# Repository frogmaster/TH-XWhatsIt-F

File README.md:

Derived from:

https://github.com/listofoptions/TH-XWhatsIt

through hole implementation of the capsense controllers by XWhatsIt
(Tom Wong-Cornell). original liscencure holds, as well as CERN OSH
(compatible license).

original implementation of Tom Wong-Cornell's controller documented here

http://downloads.cornall.co/ibm-capsense-usb-web/ibm-capsense-usb.html

component documentation is supplied, working theory of operation is under
the previous link.

Layout changed to accomodate IBM Model F PC/AT keyboard, mainly because i have that one. 
May fit other model F-s with similar setup.

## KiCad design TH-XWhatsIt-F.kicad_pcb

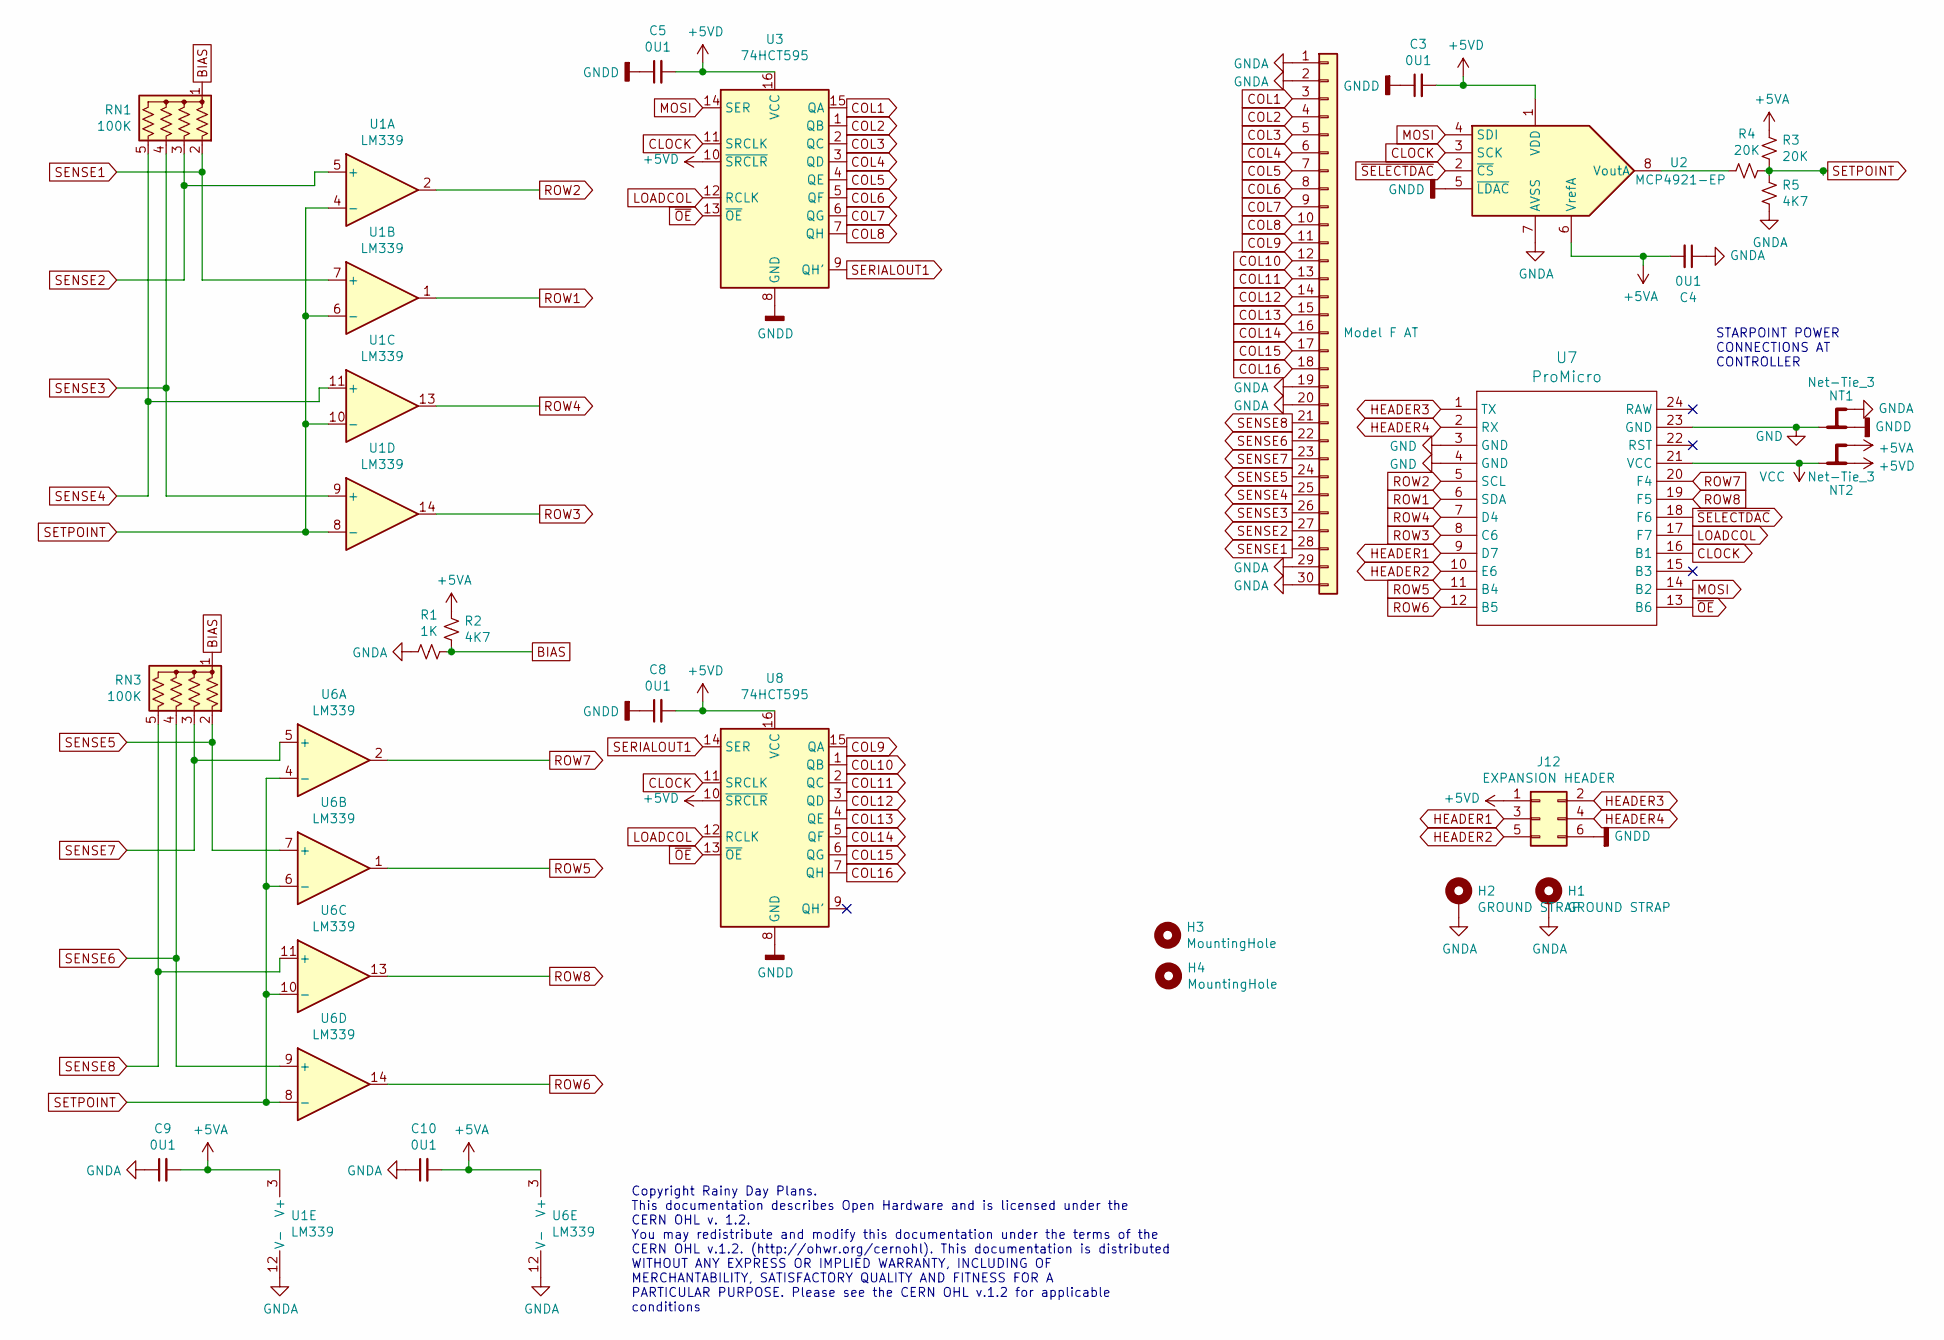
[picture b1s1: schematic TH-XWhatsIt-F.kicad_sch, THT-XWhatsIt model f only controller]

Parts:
C3, C4, C5, C8, C9, C10: 0U1; C_Disc_D3.0mm_W1.6mm_P2.50mm
H1, H2: GROUND STRAP; MountingHole_4.5mm_Pad
H3, H4: MountingHole; MountingHole_3.2mm_M3
J12: EXPANSION HEADER; PinHeader_2x03_P2.54mm_Vertical
J13: Model F AT; SIP-30-P3.96
NT1, NT2: Net-Tie_3; NetTie-3_THT_Pad1.0mm_mod_thicker
R1: 1K; R_Axial_DIN0204_L3.6mm_D1.6mm_P7.62mm_Horizontal
R2, R5: 4K7; R_Axial_DIN0204_L3.6mm_D1.6mm_P7.62mm_Horizontal
R3, R4: 20K; R_Axial_DIN0204_L3.6mm_D1.6mm_P7.62mm_Horizontal
RN1, RN3: 100K; R_Array_SIP5
U1, U6: LM339; DIP-14_W7.62mm
U2: MCP4921-EP; DIP-8_W7.62mm
U3, U8: 74HCT595; DIP-16_W7.62mm
U7: ProMicro

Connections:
+5VA: C4.2, C9.2, C10.2, NT2.3, R2.1, R3.2, U1.3 (V+), U2.6 (VrefA), U6.3 (V+)
+5VD: C3.2, C5.2, C8.2, J12.1, NT2.1, U2.1 (VDD), U3.10 (~SRCLR), U3.16 (VCC), U8.10 (~SRCLR), U8.16 (VCC)
BIAS: R1.1, R2.2, RN1.1 (common), RN3.1 (common)
CLOCK: U2.3 (SCK), U3.11 (SRCLK), U7.16 (B1), U8.11 (SRCLK)
COL1: J13.3, U3.15 (QA)
COL2: J13.4, U3.1 (QB)
COL3: J13.5, U3.2 (QC)
COL4: J13.6, U3.3 (QD)
COL5: J13.7, U3.4 (QE)
COL6: J13.8, U3.5 (QF)
COL7: J13.9, U3.6 (QG)
COL8: J13.10, U3.7 (QH)
COL9: J13.11, U8.15 (QA)
COL10: J13.12, U8.1 (QB)
COL11: J13.13, U8.2 (QC)
COL12: J13.14, U8.3 (QD)
COL13: J13.15, U8.4 (QE)
COL14: J13.16, U8.5 (QF)
COL15: J13.17, U8.6 (QG)
COL16: J13.18, U8.7 (QH)
GND: NT1.2, U7.3 (GND), U7.4 (GND), U7.23 (GND)
GNDA: C4.1, C9.1, C10.1, H1.1, H2.1, J13.1, J13.2, J13.19, J13.20, J13.29, J13.30, NT1.3, R1.2, R5.1, U1.12 (V-), U2.7 (AVSS), U6.12 (V-)
GNDD: C3.1, C5.1, C8.1, J12.6, NT1.1, U2.5 (~LDAC~), U3.8 (GND), U8.8 (GND)
HEADER1: J12.3, U7.9 (D7)
HEADER2: J12.5, U7.10 (E6)
HEADER3: J12.2, U7.1 (TX)
HEADER4: J12.4, U7.2 (RX)
LOADCOL: U3.12 (RCLK), U7.17 (F7), U8.12 (RCLK)
MOSI: U2.4 (SDI), U3.14 (SER), U7.14 (B2)
unnamed: R4.2, U2.8 (VoutA)
ROW1: U1.1, U7.6 (SDA)
ROW2: U1.2, U7.5 (SCL)
ROW3: U1.14, U7.8 (C6)
ROW4: U1.13, U7.7 (D4)
ROW5: U6.1, U7.11 (B4)
ROW6: U6.14, U7.12 (B5)
ROW7: U6.2, U7.20 (F4)
ROW8: U6.13, U7.19 (F5)
SENSE1: J13.28, RN1.2 (R1), U1.7 (+)
SENSE2: J13.27, RN1.3 (R2), U1.5 (+)
SENSE3: J13.26, RN1.4 (R3), U1.9 (+)
SENSE4: J13.25, RN1.5 (R4), U1.11 (+)
SENSE5: J13.24, RN3.2 (R1), U6.7 (+)
SENSE6: J13.22, RN3.4 (R3), U6.9 (+)
SENSE7: J13.23, RN3.3 (R2), U6.5 (+)
SENSE8: J13.21, RN3.5 (R4), U6.11 (+)
SERIALOUT1: U3.9 (QH'), U8.14 (SER)
SETPOINT: R3.1, R4.1, R5.2, U1.4 (-), U1.6 (-), U1.8 (-), U1.10 (-), U6.4 (-), U6.6 (-), U6.8 (-), U6.10 (-)
VCC: NT2.2, U7.21 (VCC)
~OE: U3.13 (~OE), U7.13 (B6), U8.13 (~OE)
~SELECTDAC: U2.2 (~CS~), U7.18 (F6)

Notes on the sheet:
Copyright Rainy Day Plans. This documentation describes Open Hardware and is licensed under the CERN OHL v. 1.2. You may redistribute and modify this documentation under the terms of the CERN OHL v.1.2. (http://ohwr.org/cernohl). This documentation is distributed WITHOUT ANY EXPRESS OR IMPLIED WARR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
STARPOINT POWER CONNECTIONS AT CONTROLLER

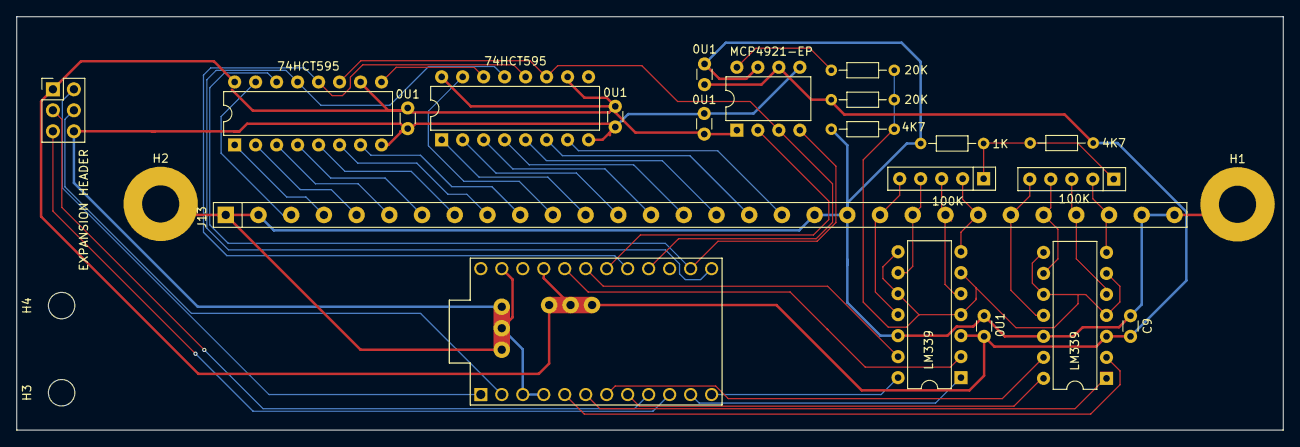
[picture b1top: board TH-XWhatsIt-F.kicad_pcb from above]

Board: 2 copper layers, 153.3 x 50.0 mm, 27 parts (0 on the bottom side), 51 nets.

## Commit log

2020-09-29 Copied and modified from TH-XWhatsIt
2020-10-01 remove old kicad files
2020-10-01 add new gerbers
2020-10-01 resize image
2020-10-01 change gerber output dir

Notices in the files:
TH-XWhatsIt-F.kicad_pcb:
Licenced under CERN OHL Version 1.2
